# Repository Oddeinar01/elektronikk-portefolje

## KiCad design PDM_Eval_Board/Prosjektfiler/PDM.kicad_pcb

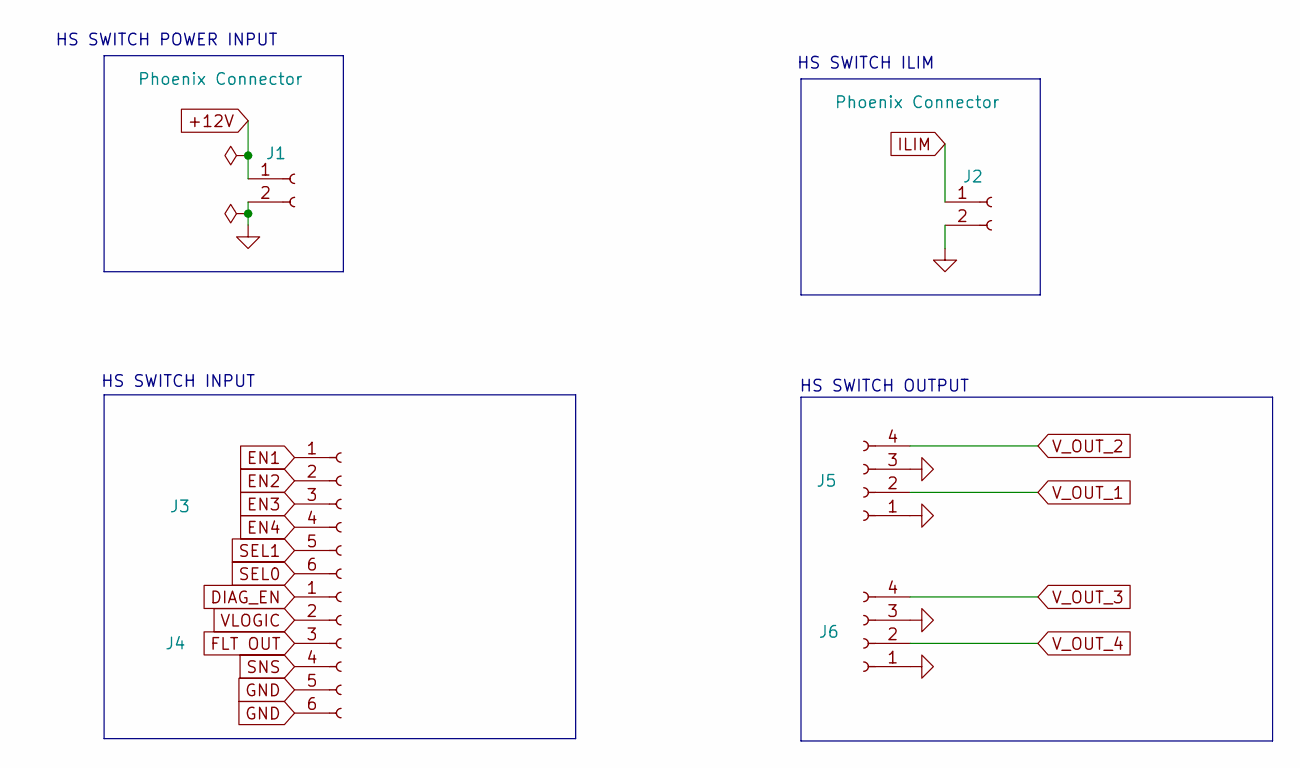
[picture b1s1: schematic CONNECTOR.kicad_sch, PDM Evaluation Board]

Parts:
J1, J2: Phoenix Connector; TerminalBlock_Phoenix_MKDS-1,5-2-5.08_1x02_P5.08mm_Horizont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; JLC Part Number C480516
J3, J4: Conn_01x06_Socket; PinSocket_1x06_P2.54mm_Vertical; JLC Part Number C40877
J5, J6: Conn_01x04_Socket; PinSocket_1x04_P2.54mm_Vertical; JLC Part Number C2718488

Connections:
+12V: J1.1; also elsewhere on the board
DIAG_EN: J4.1; also elsewhere on the board
EN1: J3.1; also elsewhere on the board
EN2: J3.2; also elsewhere on the board
EN3: J3.3; also elsewhere on the board
EN4: J3.4; also elsewhere on the board
FLT OUT: J4.3; also elsewhere on the board
GND: J1.2, J2.2, J4.5, J4.6, J5.1, J5.3, J6.1, J6.3; also elsewhere on the board
ILIM: J2.1; also elsewhere on the board
SEL0: J3.6; also elsewhere on the board
SEL1: J3.5; also elsewhere on the board
SNS: J4.4; also elsewhere on the board
VLOGIC: J4.2; also elsewhere on the board
V_OUT_1: J5.2; also elsewhere on the board
V_OUT_2: J5.4; also elsewhere on the board
V_OUT_3: J6.4; also elsewhere on the board
V_OUT_4: J6.2; also elsewhere on the board

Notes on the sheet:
HS SWITCH ILIM
HS SWITCH OUTPUT
HS SWITCH POWER INPUT
HS SWITCH INPUT

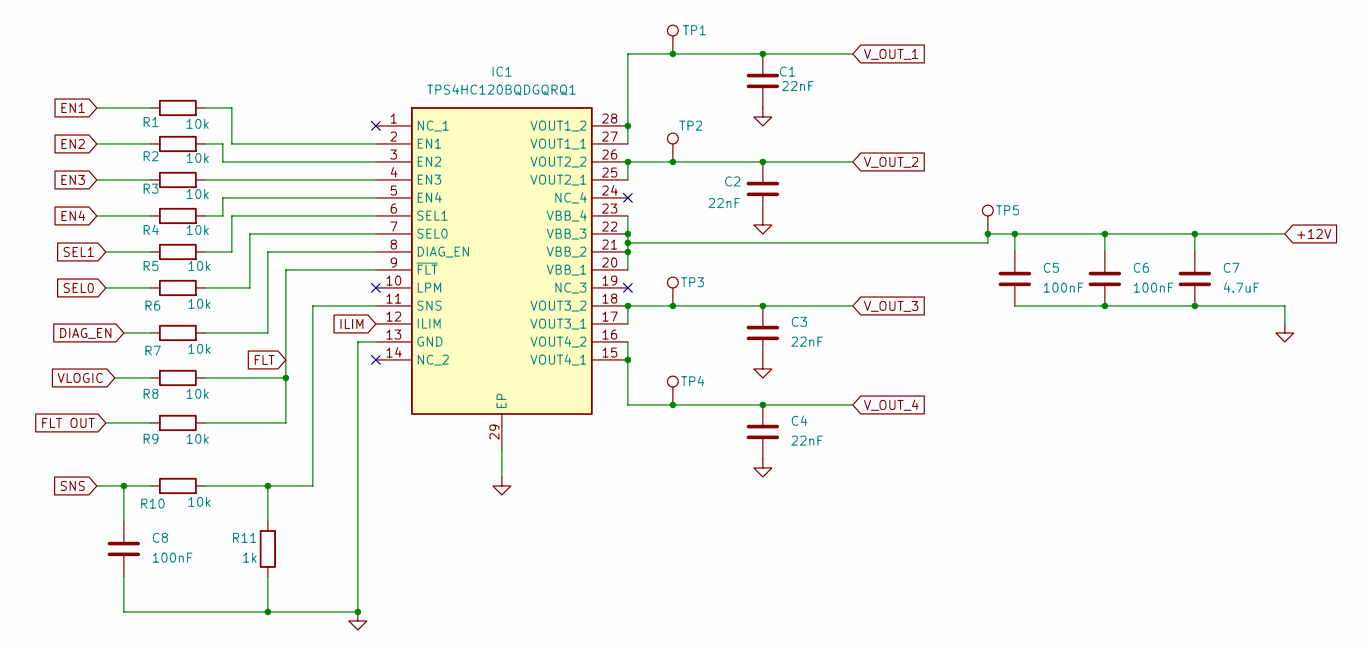
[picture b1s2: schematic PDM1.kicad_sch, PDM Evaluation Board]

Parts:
C1, C2, C3, C4: 22nF; C_0805_2012Metric_Pad1.18x1.45mm_HandSolder; JLC Part Number C1729
C5, C6, C8: 100nF; C_0805_2012Metric_Pad1.18x1.45mm_HandSolder; JLC Part Number C49678
C7: 4.7uF; C_0805_2012Metric_Pad1.18x1.45mm_HandSolder; JLC Part Number C1779
IC1: TPS4HC120BQDGQRQ1; SOP50P490X110-29N; Manufacturer_Part_Number TPS4HC120BQDGQRQ1; JLC Part Number C49406816
R1, R2, R3, R4, R5, R6, R7, R8, R9, R10: 10k; R_0805_2012Metric_Pad1.20x1.40mm_HandSolder; JLC Part Number C17414
R11: 1k; R_0805_2012Metric_Pad1.20x1.40mm_HandSolder; JLC Part Number C17513
TP1, TP2, TP3, TP4, TP5: TestPoint; TestPoint_Pad_D2.0mm

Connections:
+12V: C5.1, C6.1, C7.1, IC1.20 (VBB_1), IC1.21 (VBB_2), IC1.22 (VBB_3), IC1.23 (VBB_4), TP5.1 (1_1); also elsewhere on the board
DIAG_EN: R7.1; also elsewhere on the board
EN1: R1.1; also elsewhere on the board
EN2: R2.1; also elsewhere on the board
EN3: R3.1; also elsewhere on the board
EN4: R4.1; also elsewhere on the board
FLT: IC1.9 (~FLT), R8.1, R9.1
FLT OUT: R9.2; also elsewhere on the board
GND: C1.1, C2.1, C3.2, C4.2, C5.2, C6.2, C7.2, C8.2, IC1.13 (GND), IC1.29 (EP), R11.1; also elsewhere on the board
ILIM: IC1.12 (ILIM); also elsewhere on the board
unnamed: IC1.8 (DIAG_EN), R7.2
unnamed: IC1.2 (EN1), R1.2
unnamed: IC1.3 (EN2), R2.2
unnamed: IC1.4 (EN3), R3.2
unnamed: IC1.5 (EN4), R4.2
unnamed: IC1.7 (SEL0), R6.2
unnamed: IC1.6 (SEL1), R5.2
unnamed: IC1.11 (SNS), R10.2, R11.2
SEL0: R6.1; also elsewhere on the board
SEL1: R5.1; also elsewhere on the board
SNS: C8.1, R10.1; also elsewhere on the board
VLOGIC: R8.2; also elsewhere on the board
V_OUT_1: C1.2, IC1.27 (VOUT1_1), IC1.28 (VOUT1_2), TP1.1 (1_1); also elsewhere on the board
V_OUT_2: C2.2, IC1.25 (VOUT2_1), IC1.26 (VOUT2_2), TP2.1 (1_1); also elsewhere on the board
V_OUT_3: C3.1, IC1.17 (VOUT3_1), IC1.18 (VOUT3_2), TP3.1 (1_1); also elsewhere on the board
V_OUT_4: C4.1, IC1.15 (VOUT4_1), IC1.16 (VOUT4_2), TP4.1 (1_1); also elsewhere on the board

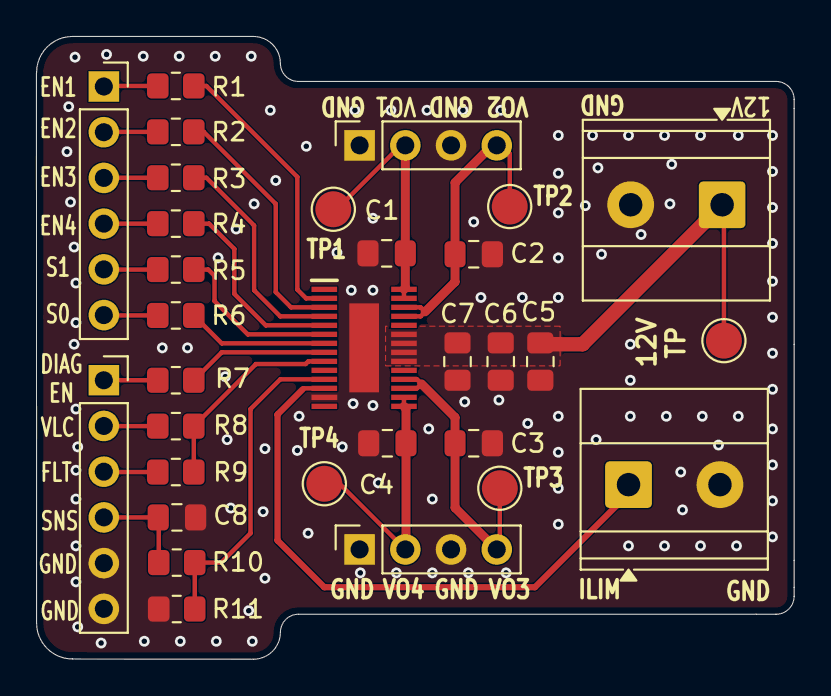
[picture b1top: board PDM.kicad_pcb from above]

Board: 2 copper layers, 42.1 x 34.6 mm, 31 parts (0 on the bottom side), 26 nets.

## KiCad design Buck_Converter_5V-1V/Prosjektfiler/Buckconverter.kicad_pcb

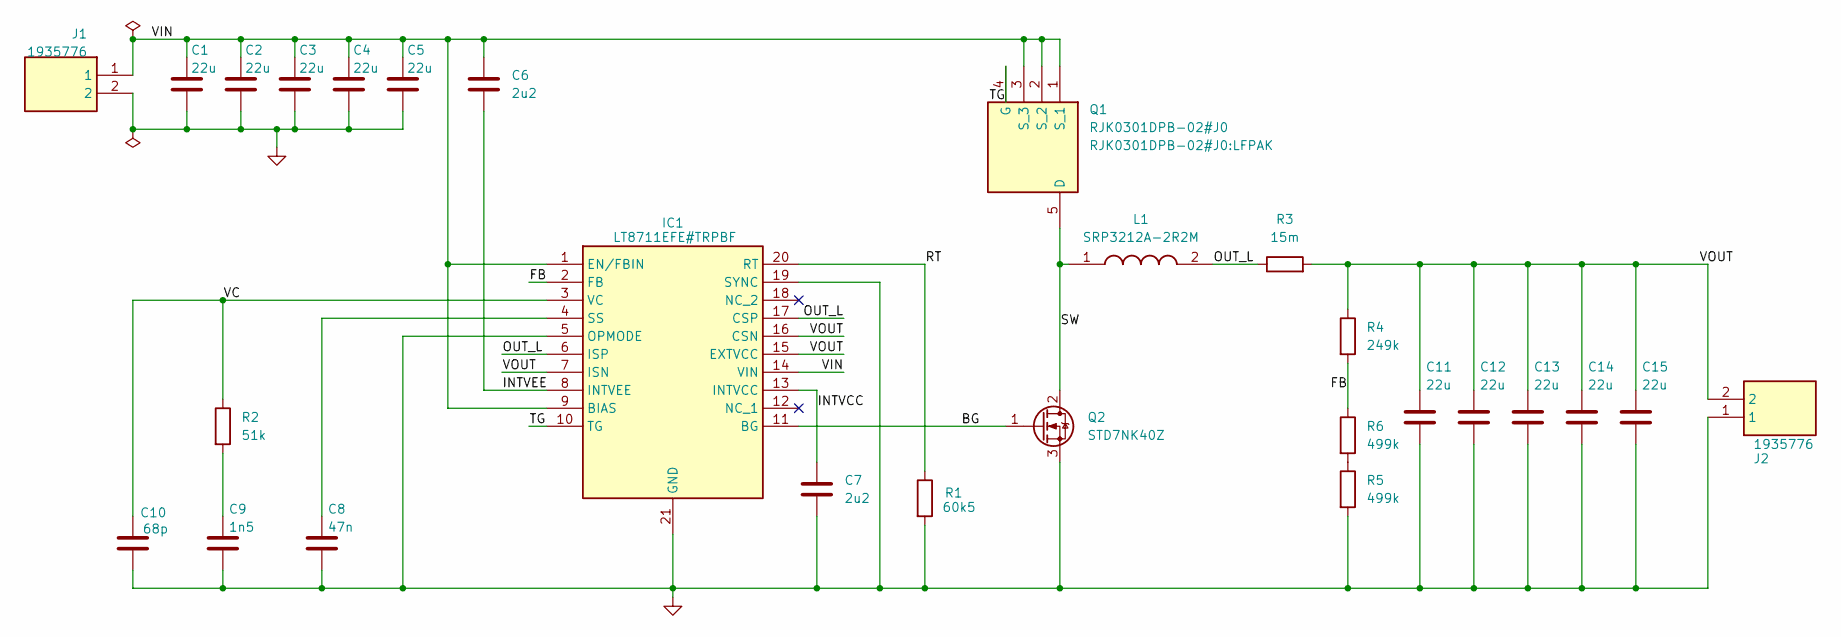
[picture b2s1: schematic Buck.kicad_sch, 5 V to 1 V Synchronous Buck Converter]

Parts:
C1, C2, C3, C4, C5: 22u; C_0805_2012Metric_Pad1.18x1.45mm_HandSolder
C6, C7: 2u2; C_0805_2012Metric_Pad1.18x1.45mm_HandSolder
C8: 47n; C_0805_2012Metric_Pad1.18x1.45mm_HandSolder
C9: 1n5; C_0805_2012Metric_Pad1.18x1.45mm_HandSolder
C10: 68p; C_0805_2012Metric_Pad1.18x1.45mm_HandSolder
C11, C12, C13, C14, C15: 22u; C_0805_2012Metric_Pad1.18x1.45mm_HandSolder; Voltage 50v
IC1: LT8711EFE#TRPBF; SOP65P640X120-21N; Manufacturer_Part_Number LT8711EFE#TRPBF; Mouser Part Number 584-LT8711EFETRPBF
J1, J2: 1935776; Manufacturer_Part_Number 1935776; Mouser Part Number 651-1935776
L1: SRP3212A-2R2M; INDC3225X120N; Manufacturer_Part_Number SRP3212A-2R2M; Mouser Part Number 652-SRP3212A-2R2M
Q1: RJK0301DPB-02#J0; LFPAK; Manufacturer_Part_Number RJK0301DPB-02#J0; Mouser Part Number 968-RJK0301DPB-02#J0
Q2: STD7NK40Z; TO-252-2
R1: 60k5; R_0805_2012Metric_Pad1.20x1.40mm_HandSolder
R2: 51k; R_0805_2012Metric_Pad1.20x1.40mm_HandSolder
R3: 15m
R4: 249k; R_0805_2012Metric_Pad1.20x1.40mm_HandSolder
R5, R6: 499k; R_0805_2012Metric_Pad1.20x1.40mm_HandSolder

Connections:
/Buck/BG: IC1.11 (BG), Q2.1 (G)
/Buck/FB: IC1.2 (FB), R4.2, R6.1
/Buck/INTVCC: C7.2, IC1.13 (INTVCC)
/Buck/INTVEE: C6.2, IC1.8 (INTVEE)
/Buck/OUT_L: IC1.6 (ISP), IC1.17 (CSP), L1.2, R3.1
/Buck/RT: IC1.20 (RT), R1.1
/Buck/SW: L1.1, Q1.5 (D), Q2.2 (D)
/Buck/TG: IC1.10 (TG), Q1.4 (G)
/Buck/VC: C10.2, IC1.3 (VC), R2.1
/Buck/VIN: C1.1, C2.1, C3.1, C4.1, C5.1, C6.1, IC1.1 (EN/FBIN), IC1.9 (BIAS), IC1.14 (VIN), J1.1, Q1.1 (S_1), Q1.2 (S_2), Q1.3 (S_3)
/Buck/VOUT: C11.1, C12.1, C13.1, C14.1, C15.1, IC1.7 (ISN), IC1.15 (EXTVCC), IC1.16 (CSN), J2.2, R3.2, R4.1
GND: C1.2, C2.2, C3.2, C4.2, C5.2, C7.1, C8.1, C9.2, C10.1, C11.2, C12.2, C13.2, C14.2, C15.2, IC1.5 (OPMODE), IC1.19 (SYNC), IC1.21 (GND), J1.2, J2.1, Q2.3 (S), R1.2, R5.2
unnamed: C9.1, R2.2
unnamed: C8.2, IC1.4 (SS)
unnamed: R5.1, R6.2

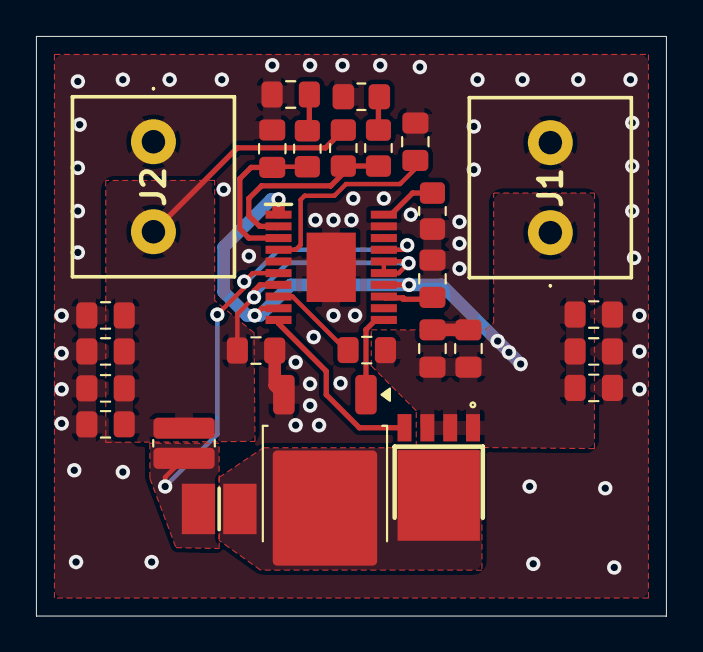
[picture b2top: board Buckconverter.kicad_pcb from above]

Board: 2 copper layers, 35.0 x 32.2 mm, 27 parts (0 on the bottom side), 15 nets.

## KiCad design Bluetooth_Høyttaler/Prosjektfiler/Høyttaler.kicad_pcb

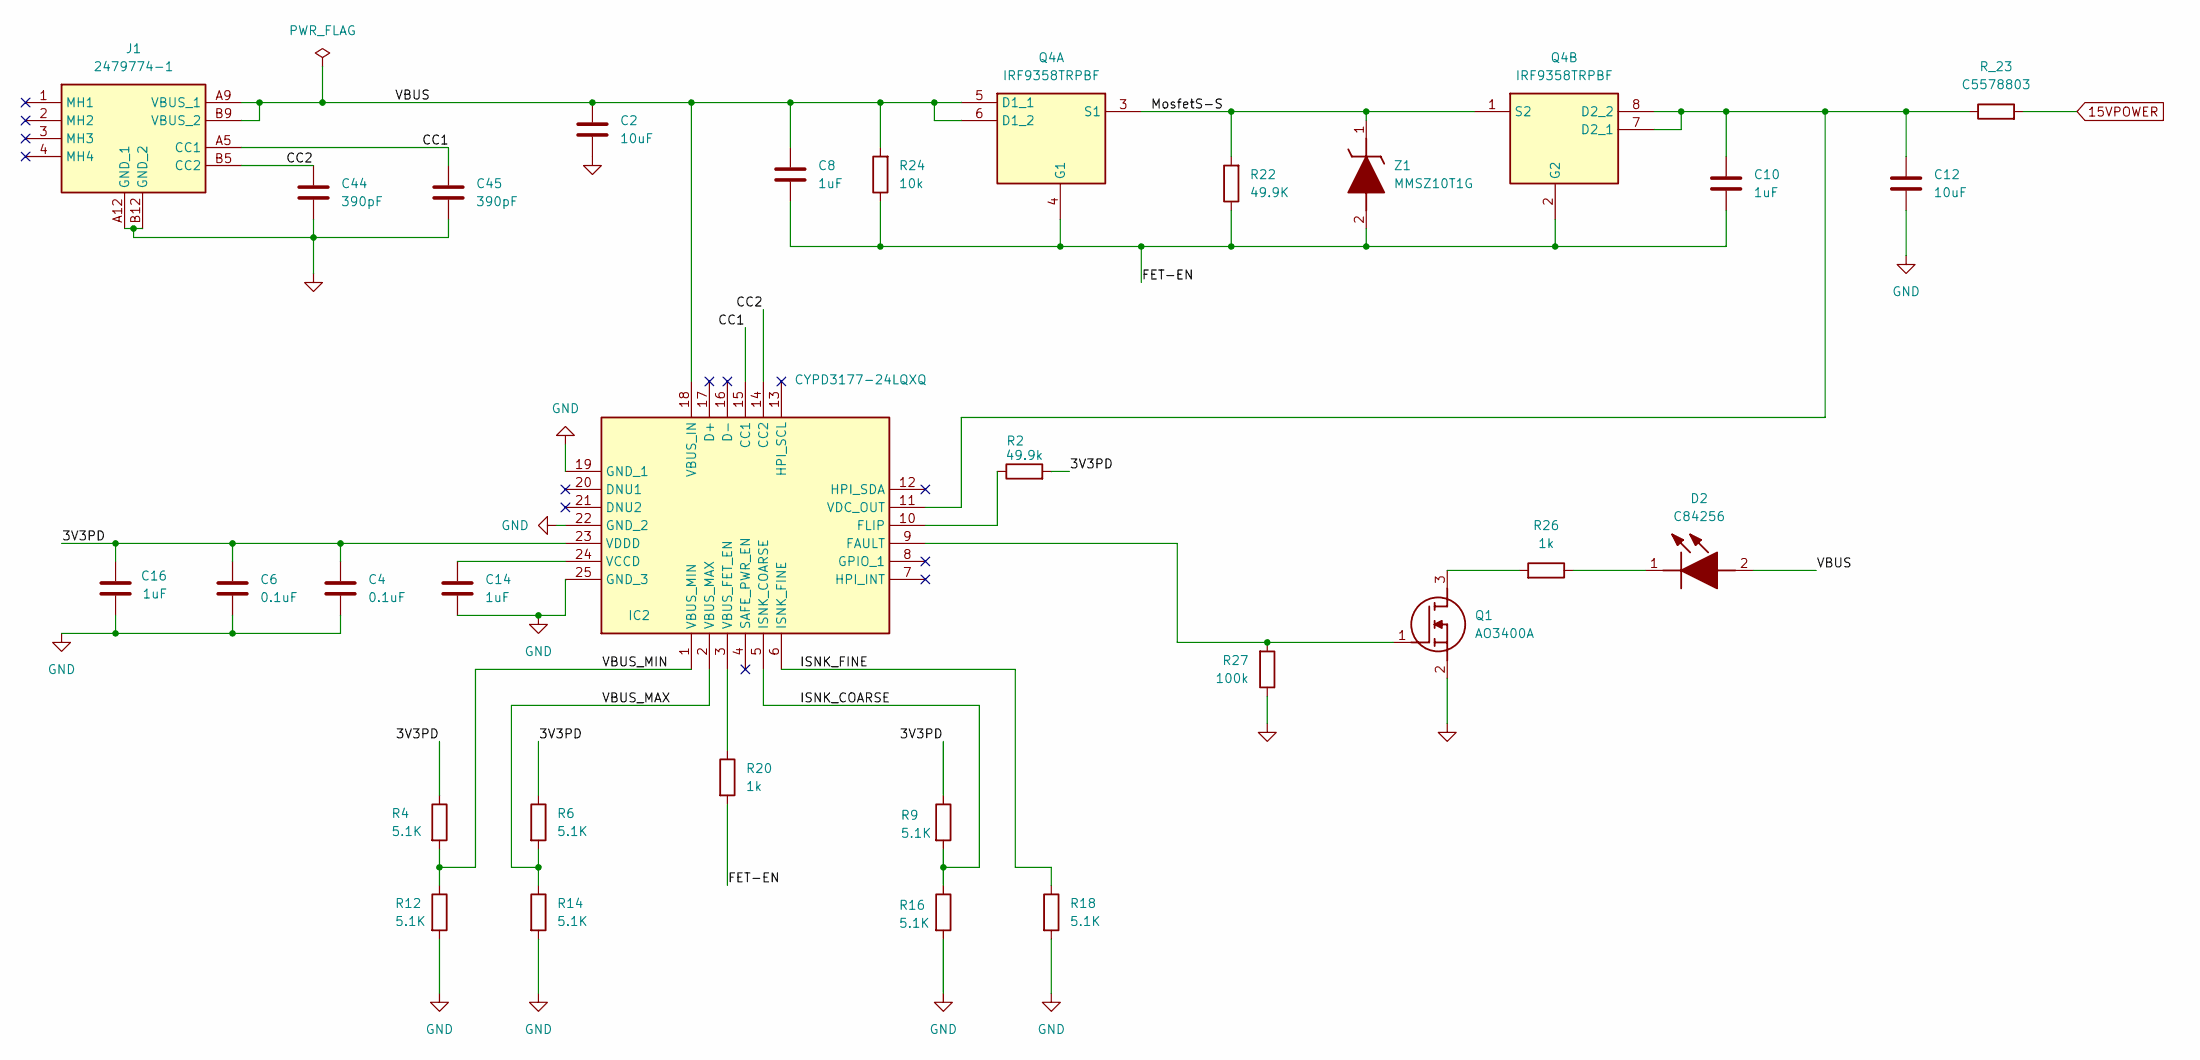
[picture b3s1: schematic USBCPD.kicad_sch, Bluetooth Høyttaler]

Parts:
C2, C12: 10uF; C_0805_2012Metric_Pad1.18x1.45mm_HandSolder; Manufacturer_Part_Number C2012X5R1V106M085AC; Mouser_Part_Number 810-C2012X5R1V106M0C
C4, C6: 0.1uF; C_0805_2012Metric_Pad1.18x1.45mm_HandSolder; Manufacturer_Part_Number AC0805KRX7R7BB104; Mouser_Part_Number 603-AC805KRX7R7BB104
C8, C10, C14, C16: 1uF; C_0805_2012Metric_Pad1.18x1.45mm_HandSolder; Manufacturer_Part_Number CGA4J3X7R1V105K125AB; Mouser_Part_Number 810-CGA4J3X7R1V105K
C44, C45: 390pF; C_0805_2012Metric_Pad1.18x1.45mm_HandSolder; Manufacturer_Part_Number 0805CG391J500NT
D2: C84256; NCD0805R1; Manufacturer_Part_Number NCD0805R1
IC2: CYPD3177-24LQXQ; QFN50P400X400X60-25N-D; Manufacturer_Part_Number CYPD3177-24LQXQ; Mouser Part Number 727-CYPD3177-24LQXQ
J1: 2479774-1; 24797741; Manufacturer_Part_Number 2479774-1; Mouser Part Number 571-2479774-1
Q1: AO3400A; SOT95P280X125-3N; Manufacturer_Part_Number AO3400A
Q4: IRF9358TRPBF; SOIC127P600X175-8N; Manufacturer_Part_Number IRF9358TRPBF; Mouser Part Number 942-IRF9358TRPBF
R2: 49.9k; R_0805_2012Metric_Pad1.20x1.40mm_HandSolder; Manufacturer_Part_Number AF0805FR-0749K9L; Mouser_Part_Number 603-AF0805FR-0749K9L
R4, R6, R9, R12, R14, R16, R18: 5.1K; R_0805_2012Metric_Pad1.20x1.40mm_HandSolder; Manufacturer_Part_Number RC0805FR-075K1L; Mouser_Part_Number 603-RC0805FR-075K1L
R20, R26: 1k; R_0805_2012Metric_Pad1.20x1.40mm_HandSolder; Manufacturer_Part_Number AS08J1001ET; Mouser_Part_Number 588-AS08J1001ET
R22: 49.9K; R_0805_2012Metric_Pad1.20x1.40mm_HandSolder; Manufacturer_Part_Number AF0805FR-0749K9L; Mouser_Part_Number 603-AF0805FR-0749K9L
R24: 10k; R_0805_2012Metric_Pad1.20x1.40mm_HandSolder; Manufacturer_Part_Number CRCW080510K0JNEA; Mouser_Part_Number 71-CRCW0805J-10K-E3
R27: 100k; R_0603_1608Metric_Pad0.98x0.95mm_HandSolder; Manufacturer_Part_Number RCA0603100KFKEC; Mouser_Part_Number 71-RCA0603100KFKEC
R_23: C5578803; R_1206_3216Metric_Pad1.30x1.75mm_HandSolder; Manufacturer_Part_Number CRF1206-J/-000ELF; Mouser_Part_Number 652-CRF1206-J-000ELF
Z1: MMSZ10T1G; SOD3716X135N; Manufacturer_Part_Number MMSZ10T1G; Mouser Part Number 863-MMSZ10T1G

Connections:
15VPOWER: R_23.2; also elsewhere on the board
/USB-C PD/3V3PD: C4.1, C6.1, C16.1, IC2.23 (VDDD), R2.2, R4.1, R6.1, R9.1
/USB-C PD/CC1: C45.1, IC2.15 (CC1), J1.A5 (CC1)
/USB-C PD/CC2: C44.1, IC2.14 (CC2), J1.B5 (CC2)
/USB-C PD/FET-EN: C8.2, C10.2, Q4.2 (G2), Q4.4 (G1), R20.2, R22.1, R24.1, Z1.2 (A)
/USB-C PD/ISNK_COARSE: IC2.5 (ISNK_COARSE), R9.2, R16.1
/USB-C PD/ISNK_FINE: IC2.6 (ISNK_FINE), R18.1
/USB-C PD/MosfetS-S: Q4.1 (S2), Q4.3 (S1), R22.2, Z1.1 (K)
/USB-C PD/VBUS: C2.1, C8.1, D2.2 (A), IC2.18 (VBUS_IN), J1.A9 (VBUS_1), J1.B9 (VBUS_2), Q4.5 (D1_1), Q4.6 (D1_2), R24.2
/USB-C PD/VBUS_MAX: IC2.2 (VBUS_MAX), R6.2, R14.1
/USB-C PD/VBUS_MIN: IC2.1 (VBUS_MIN), R4.2, R12.1
GND: C2.2, C4.2, C6.2, C12.2, C14.2, C16.2, C44.2, C45.2, IC2.19 (GND_1), IC2.22 (GND_2), IC2.25 (GND_3), J1.A12 (GND_1), J1.B12 (GND_2), Q1.2 (S), R12.2, R14.2, R16.2, R18.2, R27.1; also elsewhere on the board
unnamed: D2.1 (K), R26.1
unnamed: IC2.9 (FAULT), Q1.1 (G), R27.2
unnamed: IC2.10 (FLIP), R2.1
unnamed: IC2.3 (VBUS_FET_EN), R20.1
unnamed: C14.1, IC2.24 (VCCD)
unnamed: C10.1, C12.1, IC2.11 (VDC_OUT), Q4.7 (D2_1), Q4.8 (D2_2), R_23.1
unnamed: Q1.3 (D), R26.2

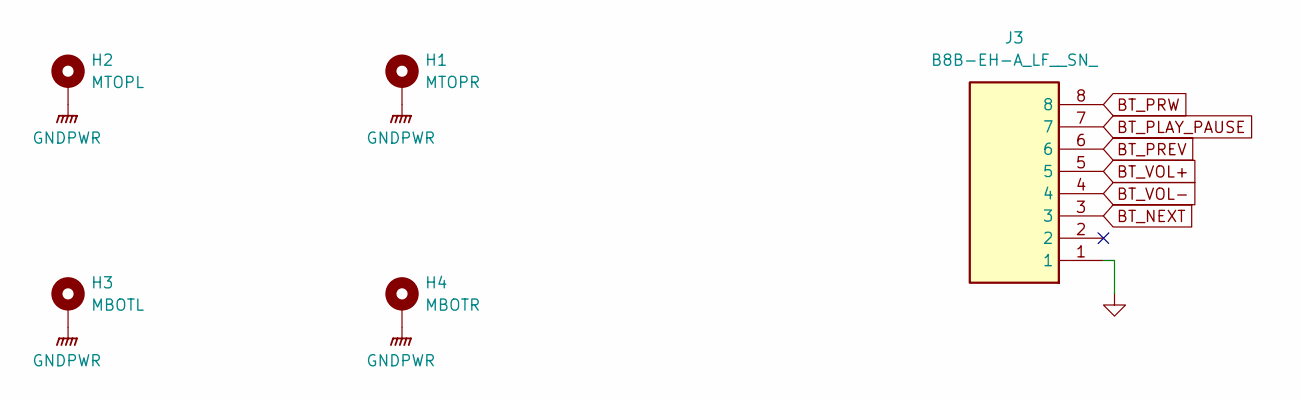
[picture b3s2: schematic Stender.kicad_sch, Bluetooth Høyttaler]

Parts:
H1: MTOPR; MountingHole_3.2mm_M3_Pad_TopBottom
H2: MTOPL; MountingHole_3.2mm_M3_Pad_TopBottom
H3: MBOTL; MountingHole_3.2mm_M3_Pad_TopBottom
H4: MBOTR; MountingHole_3.2mm_M3_Pad_TopBottom
J3: B8B-EH-A_LF__SN_; SHDR8W64P0X250_1X8_2250X380X600P; Manufacturer_Part_Number B8B-EH-A(LF)(SN); Mouser Part Number 306-B8BEHALFSNP

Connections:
BT_NEXT: J3.3; also elsewhere on the board
BT_PLAY_PAUSE: J3.7; also elsewhere on the board
BT_PREV: J3.6; also elsewhere on the board
BT_PRW: J3.8; also elsewhere on the board
BT_VOL+: J3.5; also elsewhere on the board
BT_VOL-: J3.4; also elsewhere on the board
GND: J3.1; also elsewhere on the board

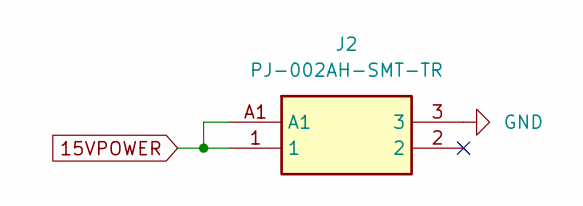
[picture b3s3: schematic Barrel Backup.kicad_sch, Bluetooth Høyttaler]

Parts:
J2: PJ-002AH-SMT-TR; PJ002AHSMTTR; Manufacturer_Part_Number PJ-002AH-SMT-TR; Mouser Part Number 490-PJ-002AH-SMT-TR

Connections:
15VPOWER: J2.1, J2.A1; also elsewhere on the board
GND: J2.3; also elsewhere on the board

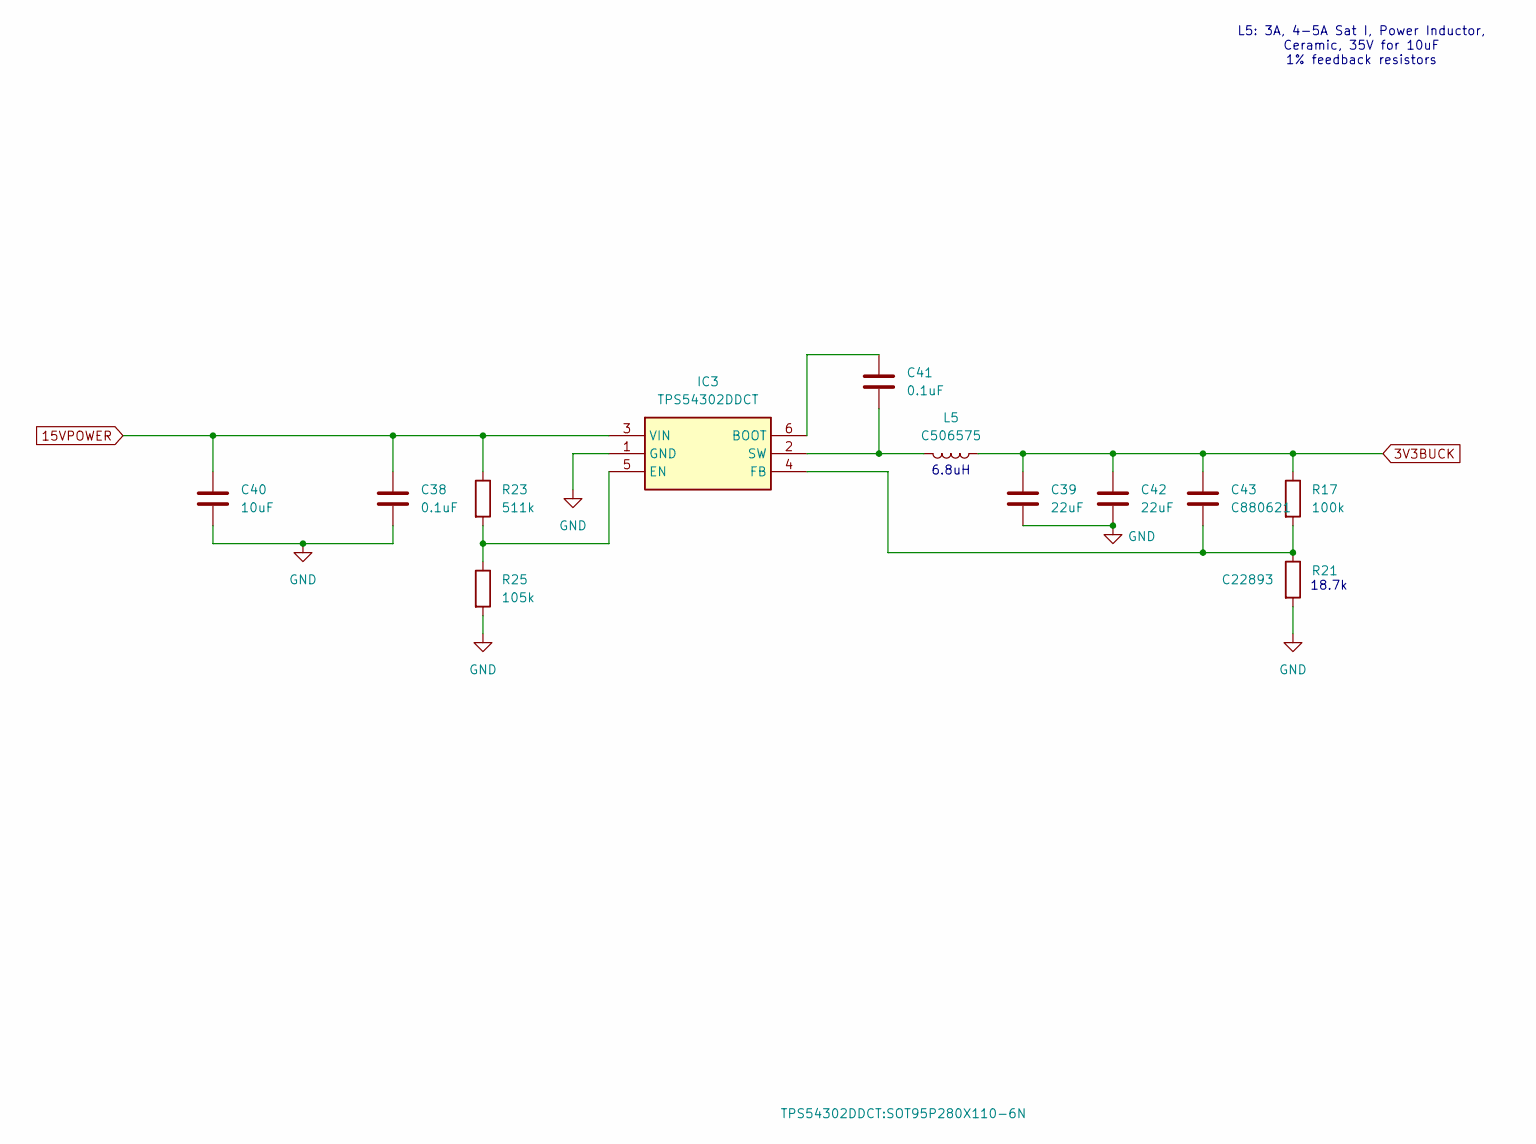
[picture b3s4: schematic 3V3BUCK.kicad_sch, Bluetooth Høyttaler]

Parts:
C38, C41: 0.1uF; C_0603_1608Metric_Pad1.08x0.95mm_HandSolder; Manufacturer_Part_Number 885012207072; Mouser_Part_Number 710-885012207072
C39, C42: 22uF; C_1206_3216Metric_Pad1.33x1.80mm_HandSolder; Manufacturer_Part_Number 1206X226M160CT; Mouser_Part_Number 791-1206X226M160CT
C40: 10uF; C_1206_3216Metric_Pad1.33x1.80mm_HandSolder; Manufacturer_Part_Number MLAST32NSB5106MTNA01; Mouser_Part_Number 963-MLAST32NSB5106MT
C43: C880621; C_0402_1005Metric_Pad0.74x0.62mm_HandSolder; Manufacturer_Part_Number TCC0402COG470J500AT
IC3: TPS54302DDCT; SOT95P280X110-6N; Manufacturer_Part_Number TPS54302DDCT; Mouser Part Number 595-TPS54302DDCT
L5: C506575; INDPM6965X300N; Manufacturer_Part_Number IHLP2525CZER6R8M8A; Mouser_Part_Number 70-IHLP2525CZR6R8M8A
R17: 100k; R_0603_1608Metric_Pad0.98x0.95mm_HandSolder; Manufacturer_Part_Number RCA0603100KFKEC; Mouser_Part_Number 71-RCA0603100KFKEC
R21: C22893; R_0603_1608Metric_Pad0.98x0.95mm_HandSolder; Manufacturer_Part_Number CR0603-FX-2212ELF; Mouser_Part_Number 652-CR0603FX-2212ELF
R23: 511k; R_0603_1608Metric_Pad0.98x0.95mm_HandSolder; Manufacturer_Part_Number CR0603-FX-5113ELF; Mouser_Part_Number 652-CR0603FX-5113ELF
R25: 105k; R_0603_1608Metric_Pad0.98x0.95mm_HandSolder; Manufacturer_Part_Number ERJ-3EKF1053V; Mouser_Part_Number 667-ERJ-3EKF1053V

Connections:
3V3BUCK: C39.1, C42.1, C43.1, L5.1, R17.1; also elsewhere on the board
15VPOWER: C38.2, C40.2, IC3.3 (VIN), R23.1; also elsewhere on the board
GND: C38.1, C39.2, C40.1, C42.2, IC3.1 (GND), R21.2, R25.2; also elsewhere on the board
unnamed: C41.2, IC3.6 (BOOT)
unnamed: IC3.5 (EN), R23.2, R25.1
unnamed: C43.2, IC3.4 (FB), R17.2, R21.1
unnamed: C41.1, IC3.2 (SW), L5.2

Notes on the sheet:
6.8uH
L5: 3A, 4-5A Sat I, Power Inductor, Ceramic, 35V for 10uF 1% feedback resistors
18.7k

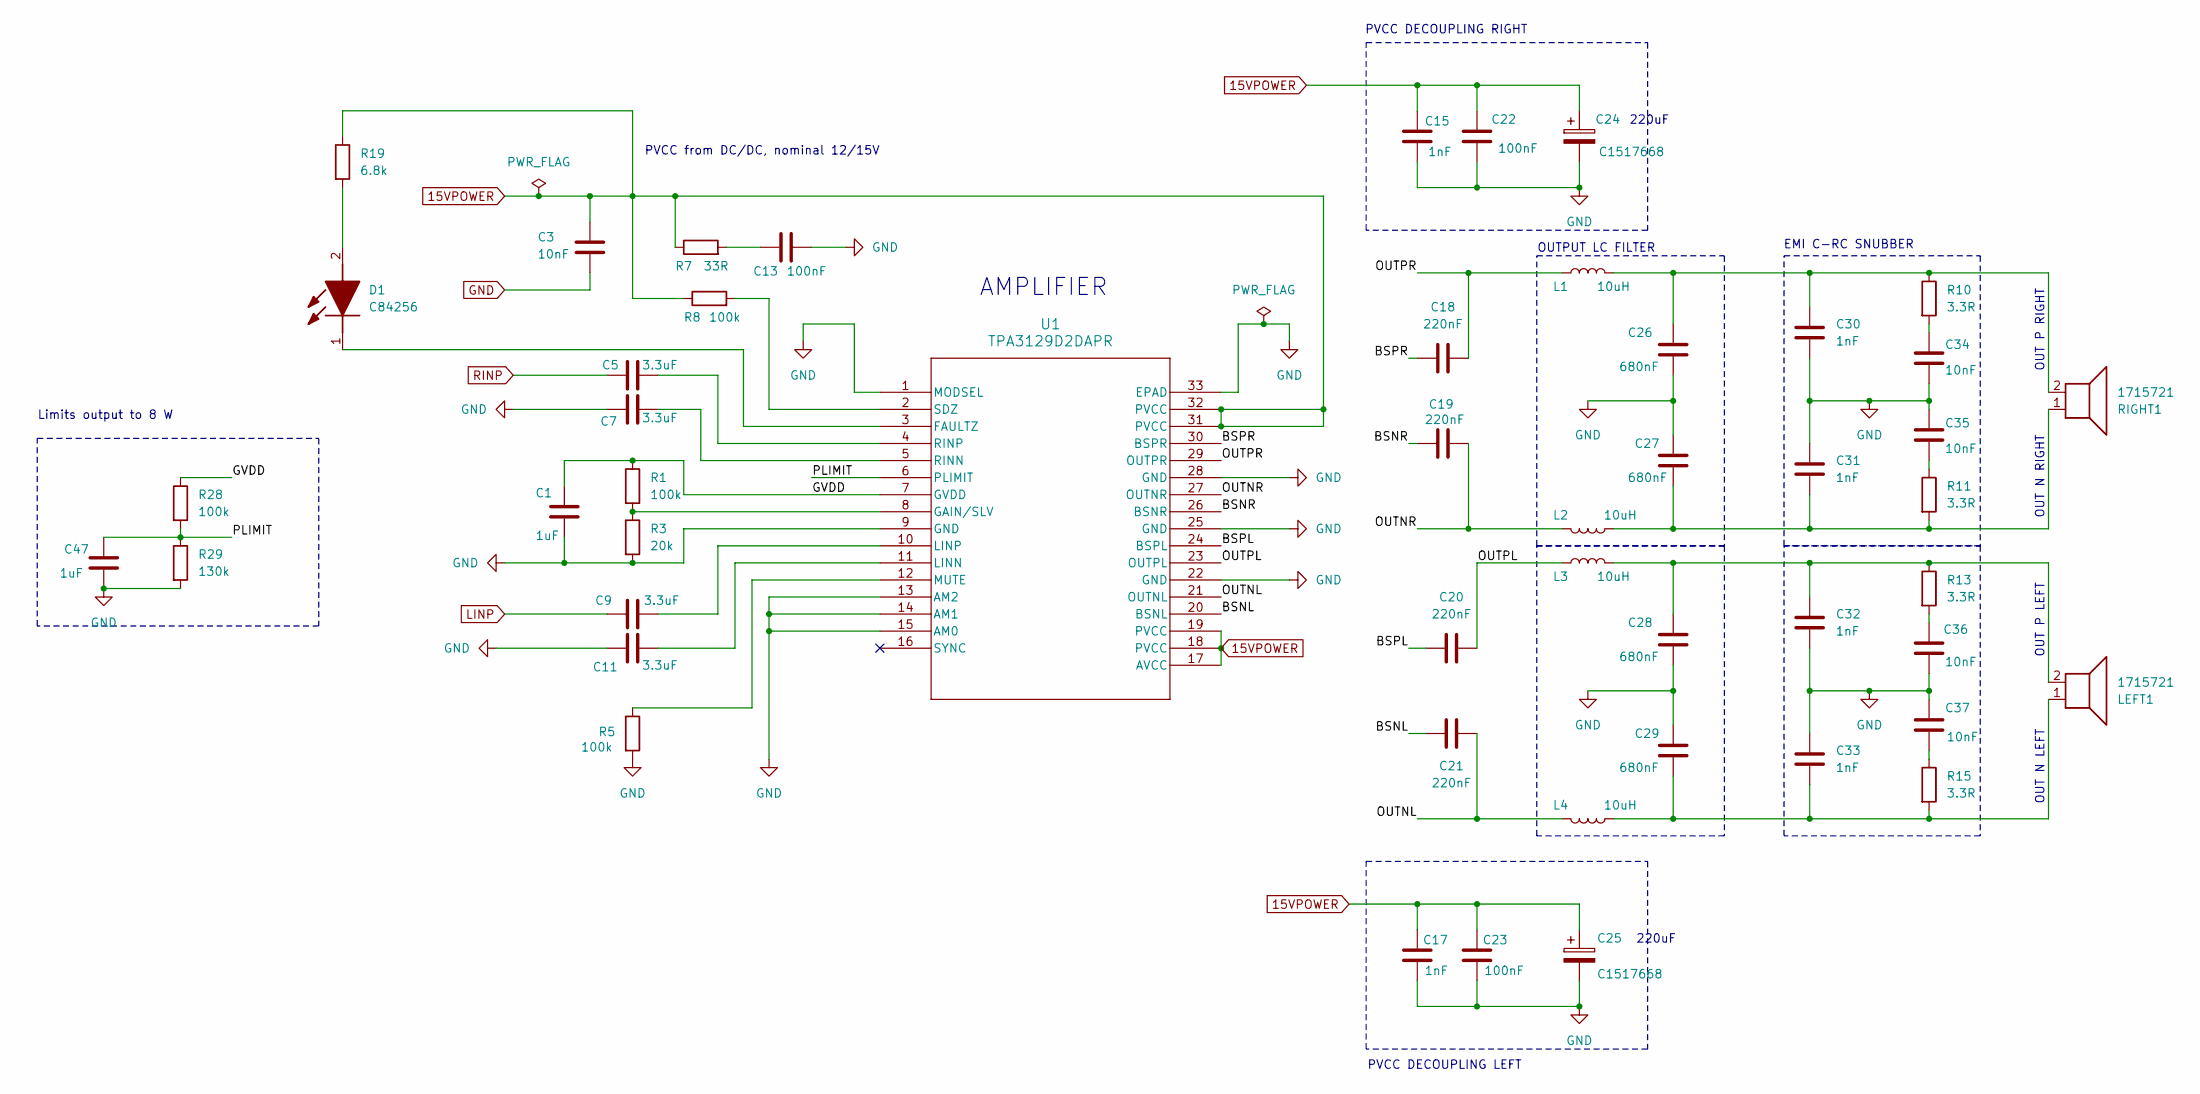
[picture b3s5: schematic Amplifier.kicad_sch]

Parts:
C1, C47: 1uF; C_0805_2012Metric_Pad1.18x1.45mm_HandSolder; Manufacturer_Part_Number KGM21AR71C105JU; Mouser_Part_Number 581-KGM21AR71C105JU
C3, C34, C35, C36, C37: 10nF; C_0603_1608Metric_Pad1.08x0.95mm_HandSolder; Manufacturer_Part_Number GCM188R71H103KA37J; Mouser_Part_Number 81-GCM188R71H103KA7J
C5, C7, C9, C11: 3.3uF; C_0805_2012Metric_Pad1.18x1.45mm_HandSolder; Manufacturer_Part_Number CL21B335KLB6PNE; Mouser_Part_Number 187-CL21B335KLB6PNE
C13, C22, C23: 100nF; C_0603_1608Metric_Pad1.08x0.95mm_HandSolder; Manufacturer_Part_Number CC0603KRX7R8BB104; Mouser_Part_Number 603-CC603KRX7R8BB104
C15, C17, C30, C31, C32, C33: 1nF; C_0603_1608Metric_Pad1.08x0.95mm_HandSolder; Manufacturer_Part_Number 0603N102K500CT; Mouser_Part_Number 791-0603N102K500CT
C18, C19, C20, C21: 220nF; C_0805_2012Metric_Pad1.18x1.45mm_HandSolder; Manufacturer_Part_Number KAM21KR71E224KU; Mouser_Part_Number 581-KAM21KR71E224KU
C24, C25: C1517668; CAPAE1030X1270N; Manufacturer_Part_Number A768MS227M1GLAS022; Mouser_Part_Number 80-A768MS227M1GLAS22
C26, C27, C28, C29: 680nF; C_1206_3216Metric_Pad1.33x1.80mm_HandSolder; Manufacturer_Part_Number CGA5L2X7R1H684K160AA; Mouser_Part_Number 810-CGA5L2X7R1H684K
D1: C84256; NCD0805R1; Manufacturer_Part_Number NCD0805R1
L1, L2, L3, L4: 10uH; INDPM6965X300N; Manufacturer_Part_Number IHLP2525CZER100MA1; Mouser_Part_Number C511066
LEFT1: 1715721; TerminalBlock_Phoenix_MKDS-1,5-2-5.08_1x02_P5.08mm_Horizont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; Manufacturer_Part_Number 1715721
R1, R5, R8, R28: 100k; R_0603_1608Metric_Pad0.98x0.95mm_HandSolder; Manufacturer_Part_Number SR0603FR-07100KL; Mouser_Part_Number 603-SR0603FR-07100KL
R3: 20k; R_0603_1608Metric_Pad0.98x0.95mm_HandSolder; Manufacturer_Part_Number RE0603FRE0720KL; Mouser_Part_Number 603-RE0603FRE0720KL
R7: 33R; R_0603_1608Metric_Pad0.98x0.95mm_HandSolder; Manufacturer_Part_Number AF0603JR-0733RL; Mouser_Part_Number 603-AF0603JR-0733RL
R10, R11, R13, R15: 3.3R; R_1206_3216Metric_Pad1.30x1.75mm_HandSolder; Manufacturer_Part_Number ERJ-UP8F3R30V; Mouser_Part_Number 667-ERJ-UP8F3R30V
R19: 6.8k; R_0805_2012Metric_Pad1.20x1.40mm_HandSolder; Manufacturer_Part_Number ERA-6AED682V; Mouser_Part_Number 667-ERA-6AED682V
R29: 130k; R_0603_1608Metric_Pad0.98x0.95mm_HandSolder; Manufacturer_Part_Number FRC0603F1303TS
RIGHT1: 1715721; TerminalBlock_Phoenix_MKDS-1,5-2-5.08_1x02_P5.08mm_Horizont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; Manufacturer_Part_Number 1715721
U1: TPA3129D2DAPR; DAP32_4P36X4P11_TEX; Manufacturer_Part_Number TPA3129D2DAPR; Mouser_Part_Number 595-TPA3129D2DAPR

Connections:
15VPOWER: C3.1, C15.1, C17.1, C22.1, C23.1, C24.1, C25.1, R7.1, R8.1, R19.1, U1.17 (AVCC), U1.18 (PVCC), U1.19 (PVCC), U1.31 (PVCC), U1.32 (PVCC); also elsewhere on the board
/Amplifier/BSNL: C21.2, U1.20 (BSNL)
/Amplifier/BSNR: C19.1, U1.26 (BSNR)
/Amplifier/BSPL: C20.1, U1.24 (BSPL)
/Amplifier/BSPR: C18.1, U1.30 (BSPR)
/Amplifier/GVDD: C1.1, R1.1, R28.1, U1.7 (GVDD)
/Amplifier/OUTNL: C21.1, L4.2, U1.21 (OUTNL)
/Amplifier/OUTNR: C19.2, L2.2, U1.27 (OUTNR)
/Amplifier/OUTPL: C20.2, L3.1, U1.23 (OUTPL)
/Amplifier/OUTPR: C18.2, L1.1, U1.29 (OUTPR)
/Amplifier/PLIMIT: C47.1, R28.2, R29.1, U1.6 (PLIMIT)
GND: C1.2, C3.2, C7.1, C11.1, C13.2, C15.2, C17.2, C22.2, C23.2, C24.2, C25.2, C26.2, C27.1, C28.2, C29.1, C30.2, C31.1, C32.2, C33.1, C34.2, C35.1, C36.2, C37.1, C47.2, R3.2, R5.2, R29.2, U1.1 (MODSEL), U1.9 (GND), U1.13 (AM2), U1.14 (AM1), U1.15 (AM0), U1.22 (GND), U1.25 (GND), U1.28 (GND), U1.33 (EPAD); also elsewhere on the board
LINP: C9.1; also elsewhere on the board
unnamed: C13.1, R7.2
unnamed: C26.1, C30.1, L1.2, R10.1, RIGHT1.2
unnamed: C27.2, C31.2, L2.1, R11.2, RIGHT1.1
unnamed: C28.1, C32.1, L3.2, LEFT1.2, R13.1
unnamed: C29.2, C33.2, L4.1, LEFT1.1, R15.2
unnamed: C34.1, R10.2
unnamed: C35.2, R11.1
unnamed: C36.1, R13.2
unnamed: C37.2, R15.1
unnamed: D1.2 (A), R19.2
unnamed: D1.1 (K), U1.3 (FAULTZ)
unnamed: R1.2, R3.1, U1.8 (GAIN/SLV)
unnamed: C11.2, U1.11 (LINN)
unnamed: C9.2, U1.10 (LINP)
unnamed: R5.1, U1.12 (MUTE)
unnamed: C7.2, U1.5 (RINN)
unnamed: C5.2, U1.4 (RINP)
unnamed: R8.2, U1.2 (SDZ)
RINP: C5.1; also elsewhere on the board

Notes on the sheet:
PVCC DECOUPLING RIGHT
OUT N LEFT
PVCC DECOUPLING LEFT
OUT P RIGHT
EMI C-RC SNUBBER
AMPLIFIER
220uF
Limits output to 8 W
PVCC from DC/DC, nominal 12/15V
OUT N RIGHT
OUT P LEFT
OUTPUT LC FILTER
